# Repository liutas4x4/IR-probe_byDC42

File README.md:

# Mini differential IR probe for Z axis, for 3D printer

This is complete set of files to reproduce fork of David Crocker's [Mini Differential IR probe](https://miscsolutions.wordpress.com/mini-height-sensor-board/). Desing is slightly changed. Implemented on Geeetech's acrylic [I3 X clone](https://www.geeetech.com/geeetech-unassembled-prusa-i3-x-3d-printer-diy-kit-p-941.html) of [Prusa I3](https://www.prusaprinters.org/prusa-i3/) 3D printer.

## PCB

It was more quick and cheap to create own PCB for this probe. Gerber files were generated using Spurkfun cam profile, copy is placed in separate directory. [Firmvare](https://github.com/dc42/OrmerodSensorBoard/tree/master/Firmware/Mini-differential-IR/V1.0_1.1) and [schematics](https://github.com/dc42/OrmerodSensorBoard/tree/master/SchematicAndPCB/Mini-differential-IR/V1.0_1.1) used can be found at original DC42's GitHub, version 1.1.

## Holding bracket

The simplest way to attach this probe to acrylic Geeetech's I3 X is to print out modified version of I3B1-31 bracket. Design is done using FreeCAD (v0.15) instead of Solidworks, for GLP purposes. Holes for screws are only 1.8 mm diam, because it is more simple job to drill exact diam for screws you will use instead of correcting CAD file. But if you would like to change something - check [modified bracket](https://github.com/liutas4x4/IR-probe_byDC42/tree/master/I3B1-31-Bracket_modified) directory.

## Connecting

This probe is connected to Z_MIN wires on GT2560. If you version of board has only 2 pins, as mine, connect GND to Ground pin of Z_MIN switch, OUT to second pin. Vcc +5 Volts you can obtain from pin on connector for motor driver.

## Calibration

Very first step - applying firmware code changes to you Marlin. Modified configuration.h and configuration_adv.h can be found at Marlin [there](https://github.com/liutas4x4/Marlin-1.1.X-Geeetech-I3-Pro-X-GT2560). Or you can do modifications you need to your specific Marlin by youself. All things you should do after uploading modified firmware are described at Daviv Crocker's [page](https://miscsolutions.wordpress.com/mini-height-sensor-board/), mentioned above.

#### As for December 23, 2017, BILINEAR and LINEAR autoleveling is not working correctly on Geeetech I3 with Marlin 1.1.6, see Issue [#7860](https://github.com/MarlinFirmware/Marlin/issues/7860) for details. After moving to 1.1.7 BILINEAR nor LINEAR still are not perfect. Under reasearch.

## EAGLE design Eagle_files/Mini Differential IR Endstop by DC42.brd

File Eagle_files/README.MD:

# Eagle files for IR Z probe

#### CAUTION: On photo you see PCB version 0.1A with wrong silkscreen marks of +5V and OUT pins. At version 0.1B there on GitHub is set of correct files.

Eagle 8.5.1 was used. Keep in mind, PCB was created using SeeedStudio and Sparkfun Eagle libraries connected. CAM job file is in the [separate directory](https://github.com/liutas4x4/IR-probe_byDC42/tree/master/cam_for_Eagle).

There are also all [Gerber files](https://github.com/liutas4x4/IR-probe_byDC42/tree/master/Gerber_files) ready for PCB ordering.

File BOM_to_Mouser.xlsx contains list of all parts used (BOM) with link to Mouser, except GL480E IR diodes.

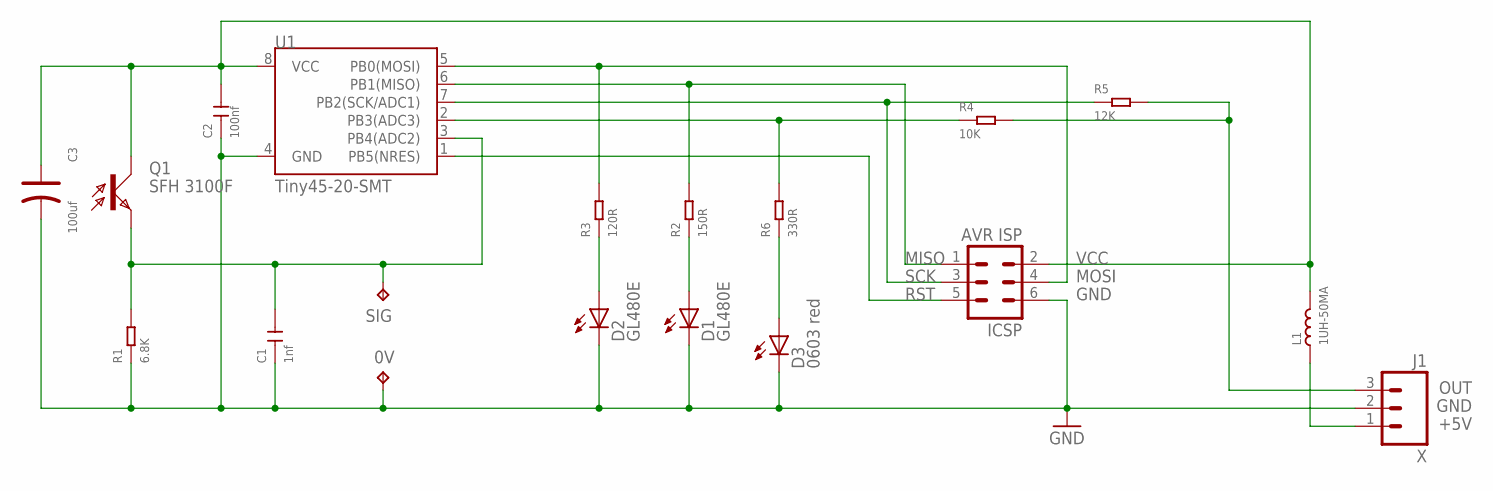
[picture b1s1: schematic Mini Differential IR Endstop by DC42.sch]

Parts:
0V: TPB1,27; B1,27
C1: 1nf; C0603
C2: 100nf; C0603
C3: 100uf; PC-D5.3MM
D1, D2: GL480E; IRL80A
D3: 0603 red; CHIP-LED0603
ICSP: AVR ISP; MA03-2
J1: X; 1X03_LOCK
L1: 1UH-50MA; L0805
Q1: SFH 3100F; SIDELOOKER
R1: 6.8K; R0603
R2: 150R; R0603
R3: 120R; R0603
R4: 10K; R0603
R5: 12K; R0603
R6: 330R; R0603
SIG: TPB1,27; B1,27
U1: Tiny45-20-SMT; SO08-EIAJ

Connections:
+5V: J1.1, L1.1
GND: 0V.TP, C1.1, C2.1, C3.-, D1.K (C), D2.K (C), D3.C, ICSP.6, J1.2, R1.1, U1.4 (GND)
MISO: ICSP.1, R2.2, U1.6 (PB1(MISO))
MOSI: ICSP.4, R3.2, U1.5 (PB0(MOSI))
unnamed: R4.1, R6.2, U1.2 (PB3(ADC3))
unnamed: D1.A, R2.1
unnamed: D2.A, R3.1
unnamed: D3.A, R6.1
unnamed: C1.2, Q1.K (E), R1.2, SIG.TP, U1.3 (PB4(ADC2))
OUT: J1.3, R4.2, R5.2
RST: ICSP.5, U1.1 (PB5(NRES))
SCK: ICSP.3, R5.1, U1.7 (PB2(SCK/ADC1))
VCC: C2.2, C3.+, ICSP.2, L1.2, Q1.A (C), U1.8 (VCC)

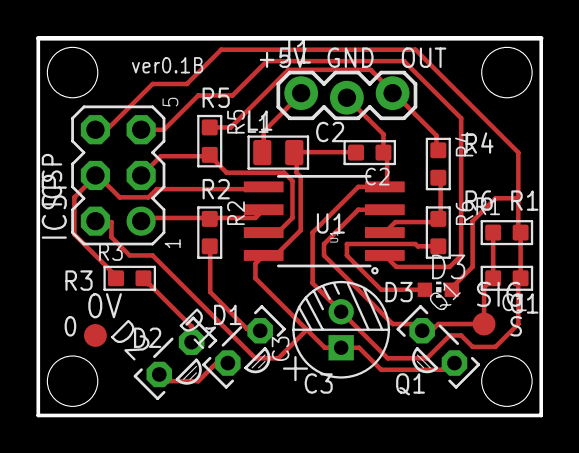
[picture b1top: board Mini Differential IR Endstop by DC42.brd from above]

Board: 2 copper layers, 27.9 x 21.0 mm, 19 parts (0 on the bottom side), 13 nets.

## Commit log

2017-12-23 Ver 0.1B
    Complete Eagle and Gerber files.
2017-12-23 Holder for IR probe
    Open FreeCAD, stl and Gcode.
2017-12-23 readme
2017-12-26 1.1.7 still not does BILINEAR correctly.
    It is possible, that for version 1.1 of IR probe, while measurement error is in acceptable range by M48 test in particular point, is mot tolerant to uneven IR properties of borosilicate glass and it'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
2020-05-01 Correction of readme
    Typo
2020-05-01 Readme corrections
    Exp of 115

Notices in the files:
parts and their libraries:
SparkFun-DigitalIC: Licensing: Creative Commons ShareAlike 4.0 International - https://creativecommons.org/licenses/by-sa/4.0
